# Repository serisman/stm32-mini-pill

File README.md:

# stm32-mini-pill
This is a development board for (LQFP-48) STM32 microcontrollers like the STM32F103C8T6 and STM32F072C8T6.
It is effectively 1/2 of the infamous 'blue-pill'.

Hold down the BOOT0/PA15 button while powering on (or press RESET and BOOT0 together, then release RESET) to access the built-in USB DFU bootloader.  The BOOT0/PA15 button can also be used for user input while not in the bootloader.

PCB design was done using KiCad.

PCBs are available at OSHPARK (or upload the included gerber.zip to your favorite board house):
https://oshpark.com/shared_projects/8USgL5pT

## 3D Renders:

## Finished Product:

## Schematic:

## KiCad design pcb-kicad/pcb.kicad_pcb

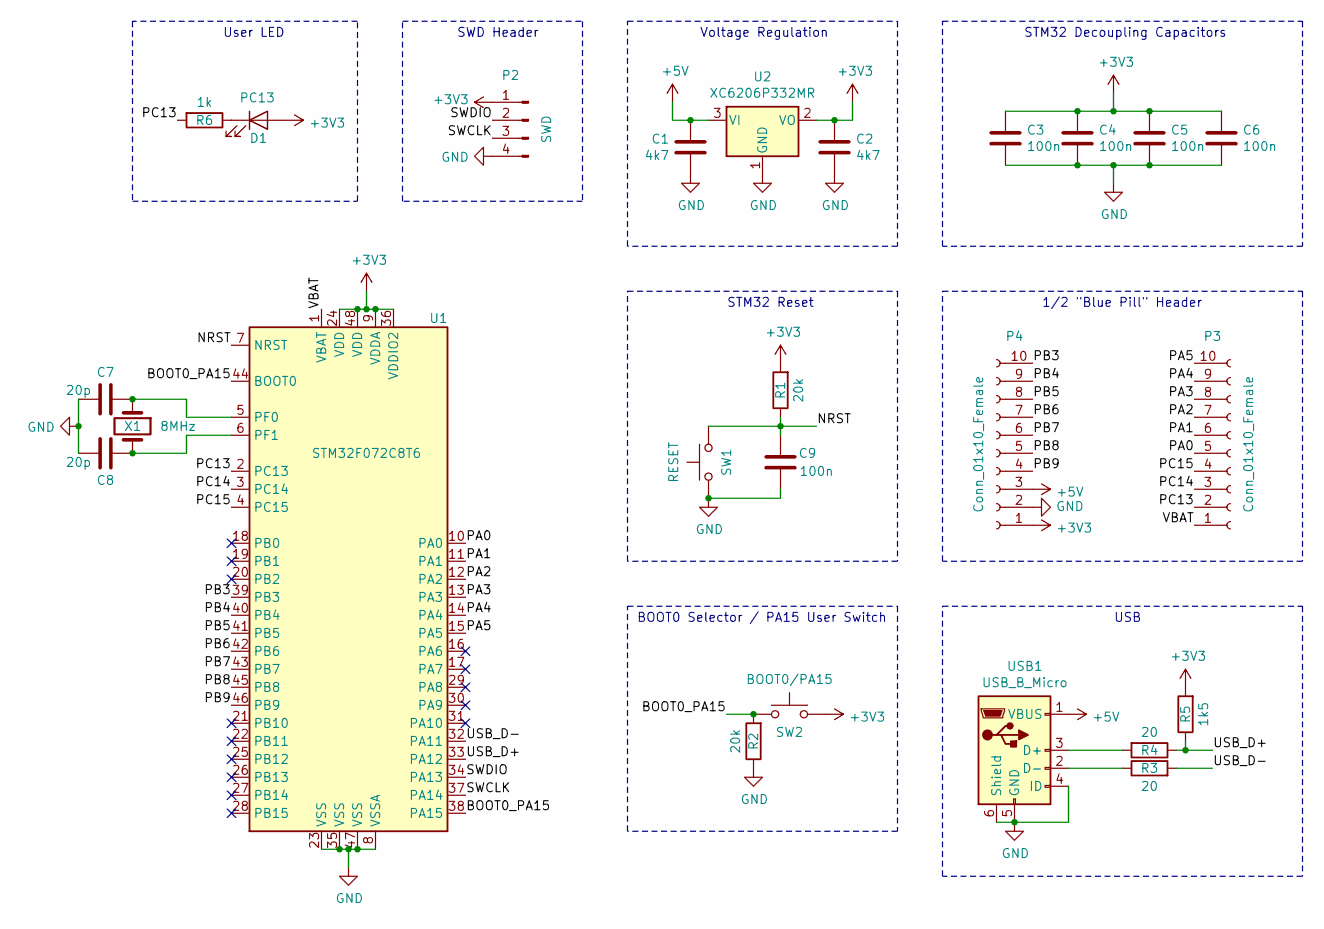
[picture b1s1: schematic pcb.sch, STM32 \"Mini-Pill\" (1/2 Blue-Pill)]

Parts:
C1, C2: 4k7; C_0805
C3, C4, C5, C6, C9: 100n; C_0805
C7, C8: 20p; C_0805
D1: PC13; LED_0805
P2: SWD; PinHeader_1x04_P2.54mm_Horizontal
P3, P4: Conn_01x10_Female; PinSocket_1x10_P2.54mm_Vertical
R1, R2: 20k; R_0805
R3, R4: 20; R_0805
R5: 1k5; R_0805
R6: 1k; R_0805
SW1: RESET; SMD-SW_Push_3.5x4.55_Side
SW2: BOOT0/PA15; SMD-SW_Push_3.5x4.55_Side
U1: STM32F072C8T6; LQFP-48_7x7mm_P0.5mm
U2: XC6206P332MR; SOT-23
USB1: USB_B_Micro; USB_Micro_B_Male
X1: 8MHz; Crystal_SMD_5032-2Pin_5.0x3.2mm

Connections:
+3V3: C2.1, C3.1, C4.1, C5.1, C6.1, D1.2 (A), P2.1, P4.1, R1.2, R5.2, SW2.1, U1.9 (VDDA), U1.24 (VDD), U1.36 (VDDIO2), U1.48 (VDD), U2.2 (VO)
+5V: C1.2, P4.3, U2.3 (VI), USB1.1 (VBUS)
/BOOT0_PA15: R2.2, SW2.2, U1.38 (PA15), U1.44 (BOOT0)
/NRST: C9.2, R1.1, SW1.2, U1.7 (NRST)
/PA0: P3.5, U1.10 (PA0)
/PA1: P3.6, U1.11 (PA1)
/PA2: P3.7, U1.12 (PA2)
/PA3: P3.8, U1.13 (PA3)
/PA4: P3.9, U1.14 (PA4)
/PA5: P3.10, U1.15 (PA5)
/PB3: P4.10, U1.39 (PB3)
/PB4: P4.9, U1.40 (PB4)
/PB5: P4.8, U1.41 (PB5)
/PB6: P4.7, U1.42 (PB6)
/PB7: P4.6, U1.43 (PB7)
/PB8: P4.5, U1.45 (PB8)
/PB9: P4.4, U1.46 (PB9)
/PC13: P3.2, R6.2, U1.2 (PC13)
/PC14: P3.3, U1.3 (PC14)
/PC15: P3.4, U1.4 (PC15)
/SWCLK: P2.3, U1.37 (PA14)
/SWDIO: P2.2, U1.34 (PA13)
/USB_D+: R4.1, R5.1, U1.33 (PA12)
/USB_D-: R3.2, U1.32 (PA11)
/VBAT: P3.1, U1.1 (VBAT)
GND: C1.1, C2.2, C3.2, C4.2, C5.2, C6.2, C7.2, C8.2, C9.1, P2.4, P4.2, R2.1, SW1.1, SW1.GND, SW2.GND, U1.8 (VSSA), U1.23 (VSS), U1.35 (VSS), U1.47 (VSS), U2.1 (GND), USB1.4 (ID), USB1.5 (GND), USB1.6 (Shield)
unnamed: C7.1, U1.5 (PF0), X1.1
unnamed: C8.1, U1.6 (PF1), X1.2
unnamed: D1.1 (K), R6.1
unnamed: R3.1, USB1.2 (D-)
unnamed: R4.2, USB1.3 (D+)

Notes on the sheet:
1/2 "Blue Pill" Header
Voltage Regulation
SWD Header
BOOT0 Selector / PA15 User Switch
STM32 Reset
USB
STM32 Decoupling Capacitors
User LED

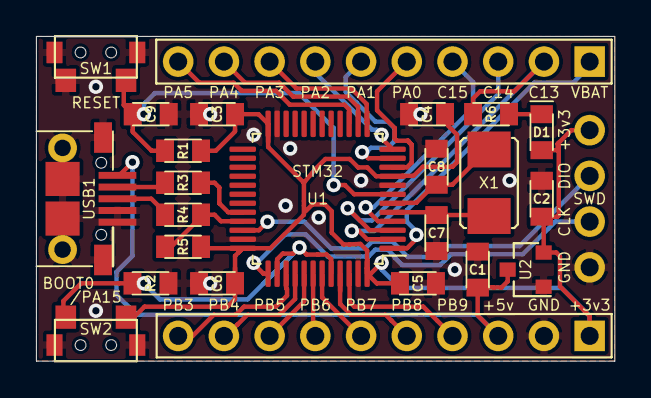
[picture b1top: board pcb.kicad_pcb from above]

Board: 2 copper layers, 32.1 x 18.0 mm, 25 parts (0 on the bottom side), 31 nets.

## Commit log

2020-06-24 Initial Commit (v1.0)
2020-06-24 Update README.md with more content and pictures
2020-06-24 Add LICENSE.md
2020-06-24 Add BOM
2020-06-24 Add kitspace.yaml
2020-06-24 Optimize BOM
